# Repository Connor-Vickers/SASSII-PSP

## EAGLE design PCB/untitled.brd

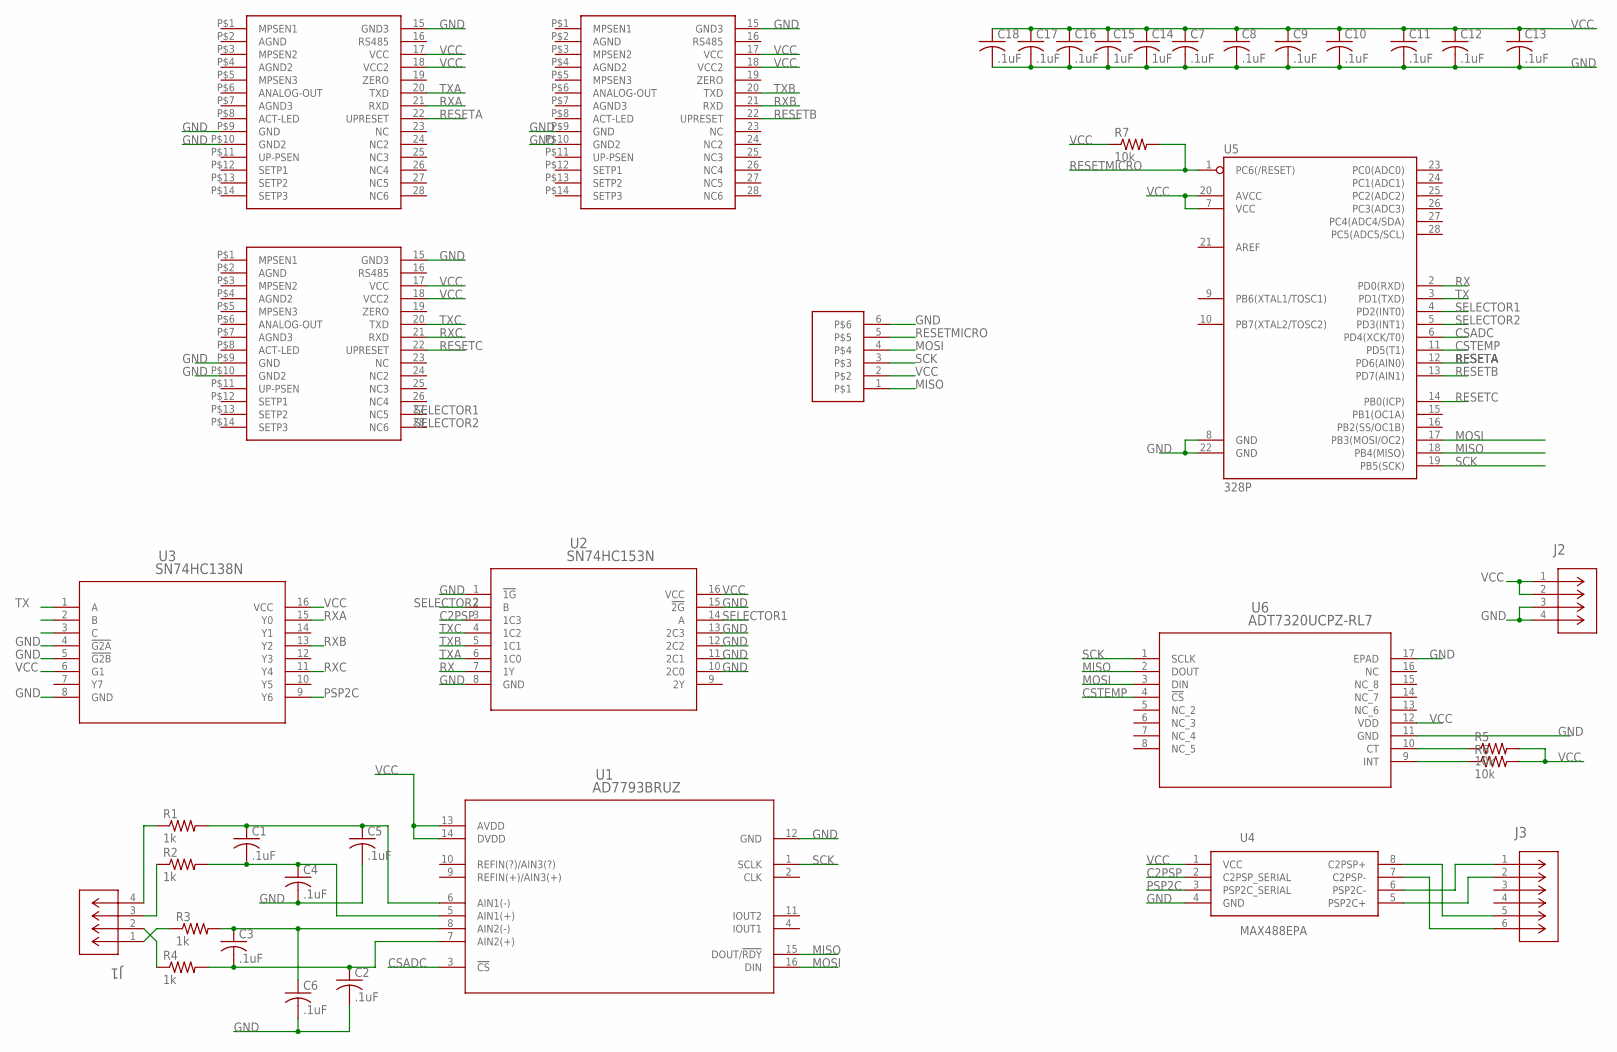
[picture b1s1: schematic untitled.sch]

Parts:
C1, C2, C3, C4, C5, C6, C7, C8, C9, C10, C11, C12, C13, C16, C17, C18: .1uF; C0603
C14, C15: 1uF; C1206
J1, J2: DF11-4
J3: DF11-6DP-2DSA(01); CON6_2X3_UF_DF11
R1, R2, R3, R4: 1k; R0603
R5, R6, R7: 10k; R0603
U1: AD7793BRUZ; RU_16
U2: SN74HC153N; N16
U3: SN74HC138N; N16
U4: MAX488EPA; DIL08
U5: 328P; DIP28
U6: ADT7320UCPZ-RL7; CP_16_17
U$1: PROGRAMMER
U$2, U$3, U$4: MKS-PIRANI; 28PIN

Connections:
C2PSP: U2.3 (1C3), U4.2 (C2PSP_SERIAL)
CSADC: U1.3 (!CS), U5.6 (PD4(XCK/T0))
CSTEMP: U5.11 (PD5(T1)), U6.4 (!CS)
GND: C2.2, C4.2, C5.2, C6.2, C7.2, C8.2, C9.2, C10.2, C11.2, C12.2, C13.2, C14.2, C15.2, C16.2, C17.2, C18.2, J2.3, J2.4, U1.12 (GND), U2.1 (!1G), U2.8 (GND), U2.10 (2C0), U2.11 (2C1), U2.12 (2C2), U2.13 (2C3), U2.15 (!2G), U3.4 (!G2A), U3.5 (!G2B), U3.8 (GND), U4.4 (GND), U5.8 (GND), U5.22 (GND), U6.11 (GND), U6.17 (EPAD), U$1.6, U$2.15 (GND3), U$2.P$9 (GND), U$2.P$10 (GND2), U$3.15 (GND3), U$3.P$9 (GND), U$3.P$10 (GND2), U$4.15 (GND3), U$4.P$9 (GND), U$4.P$10 (GND2)
MISO: U1.15 (DOUT/!RDY), U5.18 (PB4(MISO)), U6.2 (DOUT), U$1.1
MOSI: U1.16 (DIN), U5.17 (PB3(MOSI/OC2)), U6.3 (DIN), U$1.4
unnamed: J3.1, U4.6 (PSP2C-)
unnamed: J3.2, U4.5 (PSP2C+)
unnamed: J3.5, U4.8 (C2PSP+)
unnamed: J3.6, U4.7 (C2PSP-)
unnamed: C3.1, C6.1, R3.2, U1.8 (AIN2(-))
unnamed: J1.4, R1.1
unnamed: J1.3, R2.1
unnamed: J1.2, R4.1
unnamed: J1.1, R3.1
unnamed: C1.2, C4.1, R2.2, U1.5 (AIN1(+))
unnamed: C1.1, C5.1, R1.2, U1.6 (AIN1(-))
unnamed: C2.1, C3.2, R4.2, U1.7 (AIN2(+))
unnamed: R5.1, U6.10 (CT)
unnamed: R6.1, U6.9 (INT)
PSP2C: U3.9 (Y6), U4.3 (PSP2C_SERIAL)
RESETA: U5.12 (PD6(AIN0)), U$2.22 (UPRESET)
RESETB: U5.13 (PD7(AIN1)), U$4.22 (UPRESET)
RESETC: U5.14 (PB0(ICP)), U$3.22 (UPRESET)
RESETMICRO: R7.2, U5.1 (PC6(/RESET)), U$1.5
RX: U2.7 (1Y), U5.2 (PD0(RXD))
RXA: U3.15 (Y0), U$2.21 (RXD)
RXB: U3.13 (Y2), U$4.21 (RXD)
RXC: U3.11 (Y4), U$3.21 (RXD)
SCK: U1.1 (SCLK), U5.19 (PB5(SCK)), U6.1 (SCLK), U$1.3
SELECTOR1: U2.14 (A), U3.2 (B), U5.4 (PD2(INT0))
SELECTOR2: U2.2 (B), U3.3 (C), U5.5 (PD3(INT1))
TX: U3.1 (A), U5.3 (PD1(TXD))
TXA: U2.6 (1C0), U$2.20 (TXD)
TXB: U2.5 (1C1), U$4.20 (TXD)
TXC: U2.4 (1C2), U$3.20 (TXD)
VCC: C7.1, C8.1, C9.1, C10.1, C11.1, C12.1, C13.1, C14.1, C15.1, C16.1, C17.1, C18.1, J2.1, J2.2, R5.2, R6.2, R7.1, U1.13 (AVDD), U1.14 (DVDD), U2.16 (VCC), U3.6 (G1), U3.16 (VCC), U4.1 (VCC), U5.7 (VCC), U5.20 (AVCC), U6.12 (VDD), U$1.2, U$2.17 (VCC), U$2.18 (VCC2), U$3.17 (VCC), U$3.18 (VCC2), U$4.17 (VCC), U$4.18 (VCC2)

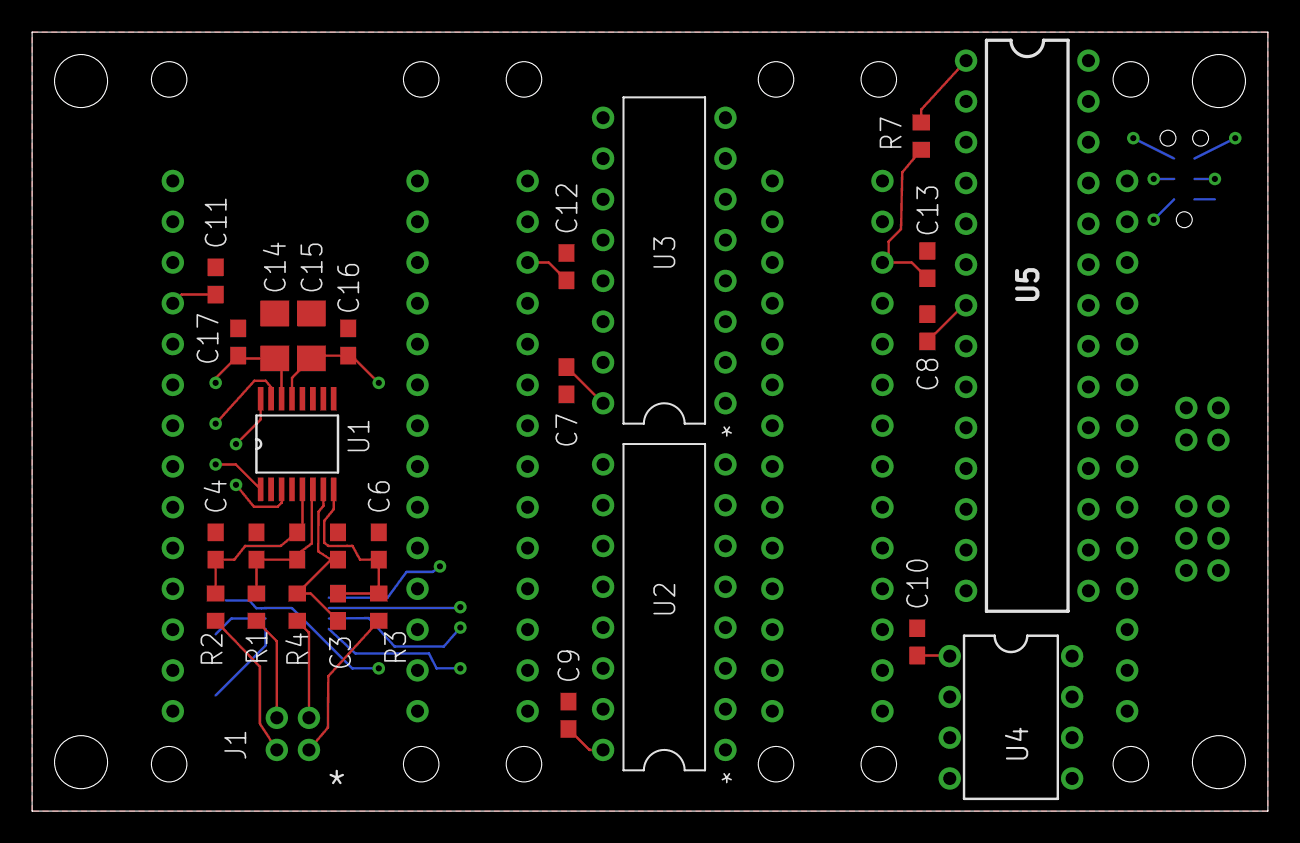
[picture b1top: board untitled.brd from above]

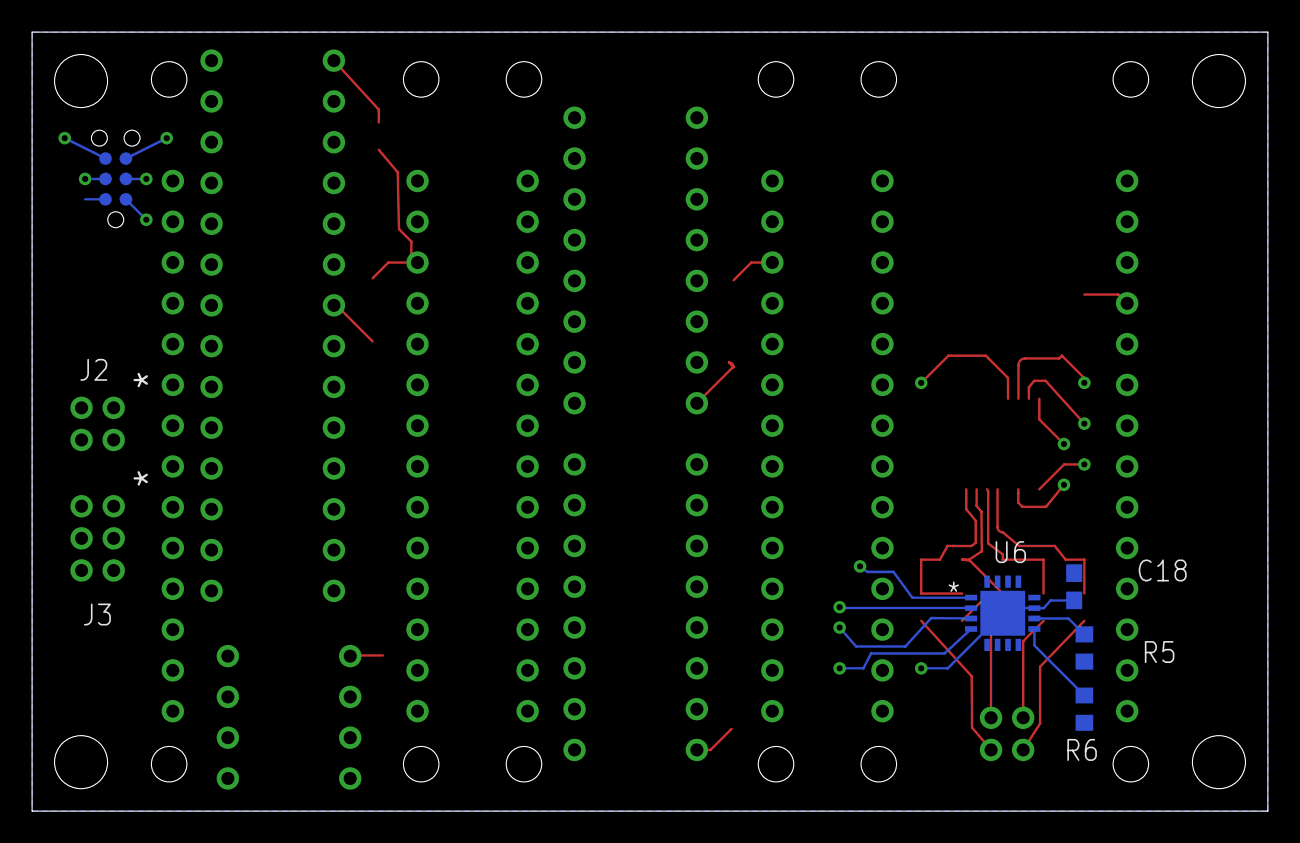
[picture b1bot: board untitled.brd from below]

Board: 4 copper layers, 77.0 x 48.5 mm, 38 parts (7 on the bottom side), 37 nets.

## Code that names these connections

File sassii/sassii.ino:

#include <SPI.h>
#include "crc.h"

#define SELECTOR1 2
#define SELECTOR2 3
#define CSADC 4
#define CSTEMP 5
#define RESETA 6
#define RESETB 7
#define RESETC 8

#define adc_query_len 4
byte adc_query[adc_query_len] = {0x58, 0xFF, 0xFF, 0xFF};
#define adc_setup_len 3
byte adc_setup[adc_setup_len] = {0x08, 0x20, 0x07};//set mode register so that conversion complete in under 80ms(time a micro pirani conversion takes) , 0x00, 0x00};

#define adc_setch1_len 3
byte adc_setch1[adc_setch1_len] = {0x10, 0x00, 0x90};
#define adc_setch2_len 3
byte adc_setch2[adc_setch2_len] = {0x10, 0x00, 0x91};


#define temp_query_len 3
byte temp_query[temp_query_len] = {0x50, 0xFF, 0xFF};
#define temp_setup_len 2
byte temp_setup[temp_setup_len] = {0x08, 0x80};
//temp startup setting
//0x8 0x80




#define buff_len 30
byte buff[buff_len];
byte temp_buff[buff_len];

#define micro_query "@253PR1?;FF"

void setup() {
  pinMode(SELECTOR1, OUTPUT);
  pinMode(SELECTOR2, OUTPUT);
  pinMode(CSADC, OUTPUT);
  pinMode(CSTEMP, OUTPUT);
  pinMode(RESETA, OUTPUT);
  pinMode(RESETB, OUTPUT);
  pinMode(RESETC, OUTPUT);

  digitalWrite(SELECTOR1, HIGH);
  digitalWrite(SELECTOR2, HIGH);
  digitalWrite(CSADC, HIGH);
  digitalWrite(CSTEMP, HIGH);
  digitalWrite(RESETA, LOW);
  digitalWrite(RESETB, LOW);
  digitalWrite(RESETC, LOW);

  Serial.begin(19200);
  Serial.setTimeout(50);
  SPI.begin();

  SPI.beginTransaction(SPISettings(100000, MSBFIRST, SPI_MODE3));

  digitalWrite(CSTEMP, LOW);
  buffcopy(temp_setup, temp_buff, 0, temp_setup_len);
  SPI.transfer(temp_buff, temp_setup_len);
  digitalWrite(CSTEMP, HIGH);

  digitalWrite(CSADC, LOW);
  buffcopy(adc_setup, temp_buff, 0, adc_setup_len);
  SPI.transfer(temp_buff, adc_setup_len);
  digitalWrite(CSADC, HIGH);
}

//general utility functions

void buffcopy(byte *from, byte *to, int starting_at, int len){
  int i;
  for(i = 0; i < len; i++){
     to[i+starting_at] = from[i];
  }
}

//functions to select which device to talk to

void selectA(){
  digitalWrite(SELECTOR1, LOW);
  digitalWrite(SELECTOR2, LOW);
}

void selectB(){
  digitalWrite(SELECTOR1, HIGH);
  digitalWrite(SELECTOR2, LOW);
}

void selectC(){
  digitalWrite(SELECTOR1, LOW);
  digitalWrite(SELECTOR2, HIGH);
}

void selectBus(){
  digitalWrite(SELECTOR1, HIGH);
  digitalWrite(SELECTOR2, HIGH);
}

//functions relating to serial

void error(){
  delay(100);
  clearSerial();
  Serial.write('?');
  Serial.flush();
}

void clearSerial(){
  while(Serial.available()){Serial.read();}
}

//crc functions

void generateCRC(int len){
  uint16_t crc = crc16(0, buff, len);
  buff[len] = crc / 0x100;
  buff[len + 1] = crc % 0x100;
}

bool isCRCbad(int len){
  uint16_t crc = crc16(0, buff, len);
  return (buff[len] !=  crc / 0x100) || (buff[len + 1] != crc % 0x100);
}

//manual command and related helper functions

void manualMicro(){
  delay(1);
  Serial.write(buff+3, buff[2]);//buff[2] = command length
  byte responceLen = Serial.readBytes(buff+3, 30);
  buff[2] = responceLen;
  generateCRC(responceLen + 3);
  selectBus();
  delay(1);
  Serial.write(buff, responceLen + 5);
}

void manualSPI(){
  int len = buff[2];//command and responce lengths are the same
  SPI.transfer(buff+3, len);
  //deselect
  digitalWrite(CSADC, HIGH);
  digitalWrite(CSTEMP, HIGH);
  //send responce
  generateCRC(len + 3);
  Serial.write(buff, len + 5);
}

void manualCommand(int readLen){

  int command_len = buff[2];
 //check that thae read length and CRC are correct
  if(readLen < 6 || readLen != command_len + 5 || isCRCbad(command_len + 3)){
    error();
    return;
  }
  
  switch(buff[1]){//switch based on sensor type
    case 0:
      digitalWrite(CSADC, LOW);
      manualSPI();
      break;
    case 1:
      digitalWrite(CSTEMP, LOW);
      manualSPI();
      break;
    case 2:
      selectA();
      manualMicro();
      break;
    case 3:
      selectB();
      manualMicro();
      break;
    case 4:
      selectC();
      manualMicro();
      break;
    default:
      error();
      break;
  }
}

//query command and related helper functions

uint16_t microConvert(){
  uint16_t returnVal = 0;
  bool onesVaild = temp_buff[0] >= '0' && temp_buff[0] <= '9';
  bool hasDecimal = temp_buff[1] == '.';
  bool tenthsVaild = temp_buff[2] >= '0' && temp_buff[2] <= '9';
  bool hundredthsValid = temp_buff[3] >= '0' && temp_buff[3] <= '9';
  bool hasExponent = temp_buff[4] == 'E';
  bool hasSign = temp_buff[5] == '-' || temp_buff[5] == '+';
  bool exponentVaild = temp_buff[6] >= '0' && temp_buff[6] <= '9';

  bool allOk = onesVaild && hasDecimal && tenthsVaild && hundredthsValid && hasExponent && hasSign && exponentVaild;
  if(allOk){
    uint16_t ones = temp_buff[0] - '0';
    uint16_t tenths = temp_buff[2] - '0';
    uint16_t hundredths = temp_buff[3] - '0';
    uint16_t exponent = temp_buff[6] - '0';
    returnVal = ones*1000 + tenths*100 + hundredths*10 + exponent;

    if(temp_buff[5] == '-'){
      returnVal += 0x8000;
    }
  }

  //clear temp_buff
  int i;
  for(i = 0; i < 7; i++){
    temp_buff[i] = 0;
  }
  return returnVal;
}

uint16_t getMicroValue(){
  delay(1);
  clearSerial();
  Serial.write(micro_query);
  Serial.readBytes(temp_buff, 7);
  if(temp_buff[0] == '@'){
    Serial.readBytes(temp_buff, 7);
  }
  return microConvert();
}

void queryCommand() {

  selectA();
  uint16_t a = getMicroValue();

  selectB();
  uint16_t b = getMicroValue();
  
  selectC();
  uint16_t c = getMicroValue();
  
  buff[0] = 'Q';

  //ADC
  
  digitalWrite(CSADC, LOW);
  //set adc to read channel 1
  buffcopy(adc_setch1, temp_buff, 0, adc_setch1_len);
  SPI.transfer(temp_buff, adc_setch1_len);
  delay(1);
  //start ADC conversion ~60ms
  buffcopy(adc_setup, temp_buff, 0, adc_setup_len);
  SPI.transfer(temp_buff, adc_setup_len);
  delay(35);
  //read adc
  buffcopy(adc_query, temp_buff, 0, adc_query_len);
  SPI.transfer(temp_buff, adc_query_len);
  buff[1] = temp_buff[1];
  buff[2] = temp_buff[2];
  buff[3] = temp_buff[3];
  delay(1);
  //set adc to read channel 2
  buffcopy(adc_setch2, temp_buff, 0, adc_setch2_len);
  SPI.transfer(temp_buff, adc_setch2_len);
  delay(1);
  //start ADC conversion ~60ms
  buffcopy(adc_setup, temp_buff, 0, adc_setup_len);
  SPI.transfer(temp_buff, adc_setup_len);
  delay(35);
  //read adc
  buffcopy(adc_query, temp_buff, 0, adc_query_len);
  SPI.transfer(temp_buff, adc_query_len);
  digitalWrite(CSADC, HIGH);
  buff[4] = temp_buff[1];
  buff[5] = temp_buff[2];
  buff[6] = temp_buff[3];


//todo adc calibration?

  digitalWrite(CSTEMP, LOW);
  buffcopy(temp_query, temp_buff, 0, temp_query_len);
  SPI.transfer(temp_buff, temp_query_len);
  digitalWrite(CSTEMP, HIGH);
  buff[7] = temp_buff[1];
  buff[8] = temp_buff[2];

  buff[9] = a / 0x100;
  buff[10] = a % 0x100;

  buff[11] = b / 0x100;
  buff[12] = b % 0x100;

  buff[13] = c / 0x100;
  buff[14] = c % 0x100;
  
  generateCRC(15);

  clearSerial();  
  selectBus();
  delay(1);
  Serial.write(buff, 17);
}


void loop() {  
  if(Serial.available()){
    delay(20);
    int readLen = Serial.readBytes(buff, Serial.available());
    switch (buff[0]) {
      case 'Q':
        queryCommand();
        break;
      case 'M':
        manualCommand(readLen);
        break;
      default:
        error();
        break;
    }
  }
  delay(10);
}

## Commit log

2017-12-06 v1 flight release
2017-12-06 removed .git in sub directory
2017-12-06 added documentation and PCB design
2017-12-16 minor improvments
